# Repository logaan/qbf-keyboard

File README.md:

# QBF — compact chorded keyboard

QBF uses two identical ten-key wireless boards that can be used separately, joined flat or used one at a time. Eight portrait 1.5U keys form a close 4 × 2 grid; two 1U keys sit above and below a recessed Seeed XIAO nRF52840 Plus in column five. Key geometry is symmetric about the horizontal midpoint so the second half can rotate 180°. There is no display or external reset button.

Each main PCB and circuit-free baseplate measures **97.7 × 58.5 mm**. The accepted key layout is wider than the original 80 mm target. Four M2 mounts and a 2.25 mm border support the printed case. A protected 301055 battery sits between the main switch rows on the intact baseplate, with a side-entry JST-SH connector and a left-facing power switch tucked inside the PCB edge.

The new case has two independent trays and rims, individual snap-on covers, and one removable underside bridge. It joins the halves with controllers facing inward. Joining, separating and uncovering require no tools; initial board installation uses screws. There is no hinge. Each covered half measures **100.9 × 63.3 × 21.2 mm**. Separate the halves for ordinary straight USB cable access.

## Build files

- [Electronics guide](ergogen-kikad/README.md), [assembly requirements](ergogen-kikad/design/ASSEMBLY.md), [Ergogen source](ergogen-kikad/design/config.yaml).
- KiCad: [main PCB](ergogen-kikad/generated/pcbs/macropad.kicad_pcb), [baseplate](ergogen-kikad/generated/pcbs/baseplate.kicad_pcb), [routing preview](ergogen-kikad/generated/routing.png).
- Case: [print bundle](modular-case/generated/qbf-print-files.zip), [assembly and printing guide](modular-case/README.md), [FreeCAD](modular-case/generated/qbf_modular_case.FCStd), [dimensioned drawing](modular-case/generated/dimensions.png).
- Firmware: [standalone XIAO UF2](ergogen-kikad/generated/firmware/qbf_macropad.uf2), [shield and keymap](ergogen-kikad/config/boards/shields/qbf_macropad/), [build validation](ergogen-kikad/generated/firmware/validation.json).

Each key is wired directly to GPIO and GND, with no diode matrix. The supplied firmware makes each half an independent USB/Bluetooth keyboard and preserves the numerical test map `1 2 3 4 9 / 5 6 7 8 0`. Configure the desired chord behaviour before treating it as a Braille input device; the test map is not a completed Braille translator.

The work was completed sequentially: Ergogen layout, routed KiCad boards and assembly clearances, firmware, then case. Both boards report zero DRC violations and zero unconnected items. The electronics and case have nominal geometric checks; native KiCad renders retain all components in cap-free inspection except the ten caps. The recessed XIAO soldering process, purchased hardware, clip durability and cover strength still require a physical prototype.

## Regeneration

Follow the electronics guide to regenerate and verify the boards, then build firmware with `./scripts/build-firmware.sh /path/to/zmk-repository`. After those stages are reviewed, run `./scripts/generate-mechanical.sh`, `./modular-case/render.sh` and `./modular-case/present.sh` sequentially. Read the [case guide](modular-case/README.md) for dependencies and print orientations.

The earlier `bumper-case/` and `mechanical/` files, and AI concept images in `assets/renders/`, are historical. They do not describe or fit the current board.

## Mikoto controller diagnostics

The separate [automated test fixture](diagnostics/mikoto/README.md) uses a SuperMini nRF52840 to reset a Mikoto, enter UF2 mode and simulate four direct keyboard inputs. It includes a wiring guide, fixture code, test firmware and a macOS USB checker. Its physical fixture remains to be assembled and tested.

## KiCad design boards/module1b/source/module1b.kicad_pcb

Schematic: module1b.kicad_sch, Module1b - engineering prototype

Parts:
AE1: Antenna; AE1
C1: 4.7uF; C1; Manufacturer Part CL05A475MP5NRNC; LCSC Part C23733
C2: 100nF; C2; Manufacturer Part CL05B104KA5NNNC; LCSC Part C1525
C3: 100nF; C3; Manufacturer Part CL05B104KA5NNNC; LCSC Part C1525
C4: 100nF; C4; Manufacturer Part CL05B104KA5NNNC; LCSC Part C1525
C5: 1pF; C5; Manufacturer Part 0402CG1R0C500NT; LCSC Part C1550
C6: 15pF; C6; Manufacturer Part 0402CG150J500NT; LCSC Part C1548
C7: 15pF; C7; Manufacturer Part 0402CG150J500NT; LCSC Part C1548
C8: 1uF; C8; Manufacturer Part CL05A105KO5NNNC; LCSC Part C52923
C9: 1pF; C9; Manufacturer Part 0402CG1R0C500NT; LCSC Part C1550
C10: 100nF; C10; Manufacturer Part CL05B104KA5NNNC; LCSC Part C1525
C11: 100pF; C11; Manufacturer Part 0402CG101J500NT; LCSC Part C1546
C12: 1nF; C12; Manufacturer Part 0402B102K500NT; LCSC Part C1523
C13: 4.7uF; C13; Manufacturer Part CL05A475MP5NRNC; LCSC Part C23733
C14: 4.7uF; C14; Manufacturer Part CL05A475MP5NRNC; LCSC Part C23733
C15: 1uF; C15; Manufacturer Part CL05A105KO5NNNC; LCSC Part C52923
C16: 47nF; C16; Manufacturer Part CL05B473KO5NNNC; LCSC Part C307434
C17: 15pF; C17; Manufacturer Part 0402CG150J500NT; LCSC Part C1548
C18: 15pF; C18; Manufacturer Part 0402CG150J500NT; LCSC Part C1548
C19: 10nF; C19; Manufacturer Part CL05B103KB5NNNC; LCSC Part C15195
C20: 4.7uF; C20; Manufacturer Part CL05A475MP5NRNC; LCSC Part C23733
C21: 10uF; C21; Manufacturer Part CL10A106KP8NNNC; LCSC Part C19702
C22: 1.5pF; C22; Manufacturer Part CL05C1R5CB5NNNC; LCSC Part C170150
C23: 1uF; C23; Manufacturer Part CL05A105KO5NNNC; LCSC Part C52923
C24: 4.7uF; C24; Manufacturer Part CL05A475MP5NRNC; LCSC Part C23733
C25: 4.7uF; C25; Manufacturer Part CL05A475MP5NRNC; LCSC Part C23733
C26: 4.7uF; C26; Manufacturer Part CL05A475MP5NRNC; LCSC Part C23733
D1: BLUE; D1; Manufacturer Part 19-217/BHC-ZL1M2RY/3T; LCSC Part C72041
D3: ORANGE; D3; Manufacturer Part E6C0603SEAC1UDA; LCSC Part C375450
D5: PMEG4010CEJ; D5; Manufacturer Part PMEG4010CEJ; LCSC Part C50704
DISP1: nice!view with 5-pin 2.54mm connector; DISP1; Manufacturer Part nice!view with 5-pin 2.54mm connector
F1: 500mA hold; F1; Manufacturer Part 0402L050SLKR; LCSC Part C206938
H1: 9774020243; H1; Manufacturer Part 9774020243R
H2: 9774020243; H2; Manufacturer Part 9774020243R
H3: 9774020243; H3; Manufacturer Part 9774020243R
H4: 9774020243; H4; Manufacturer Part 9774020243R
J1: USB_C_Receptacle_USB2.0; J1; Manufacturer Part 918-418K2024S40000; LCSC Part C168688
J2: S2B-PH-SM4-TB(LF)(SN); J2; Manufacturer Part S2B-PH-SM4-TB(LF)(SN); LCSC Part C295747
L1: 3.9nH; L1; Manufacturer Part SDCL1005C3N9STDF; LCSC Part C14033
L2: 15nH; L2; Manufacturer Part SDCL1005C15NJTDF; LCSC Part C27143
L3: 10uH; L3; Manufacturer Part LBMF1608T100K; LCSC Part C87216
L4: 10uH; L4; Manufacturer Part LBMF1608T100K; LCSC Part C87216
NT1: NetTie_2; NT1
R2: 2M; R2; Manufacturer Part RC0402FR-072ML; LCSC Part C138014
R3: 2M; R3; Manufacturer Part RC0402FR-072ML; LCSC Part C138014
R4: 10M; R4; Manufacturer Part 0402WGF1005TCE; LCSC Part C26082
R5: 1.5k; R5; Manufacturer Part 0402WGF1501TCE; LCSC Part C25867
R6: 10k; R6; Manufacturer Part 0402WGF1002TCE; LCSC Part C25744
R7: 8.66k; R7; Manufacturer Part RC0402FR-078K66L; LCSC Part C185387
R8: 10k; R8; Manufacturer Part 0402WGF1002TCE; LCSC Part C25744
R9: 5.1k; R9; Manufacturer Part 0402WGF5101TCE; LCSC Part C25905
R10: 5.1k; R10; Manufacturer Part 0402WGF5101TCE; LCSC Part C25905
R11: 0R; R11; Manufacturer Part 0402WGF0000TCE; LCSC Part C17168
R12: 2M; R12; Manufacturer Part RC0402FR-072ML; LCSC Part C138014
S1: CPG135001S30; S1; Manufacturer Part CPG135001S30; LCSC Part C5333465
S2: CPG135001S30; S2; Manufacturer Part CPG135001S30; LCSC Part C5333465
S3: CPG135001S30; S3; Manufacturer Part CPG135001S30; LCSC Part C5333465
S4: CPG135001S30; S4; Manufacturer Part CPG135001S30; LCSC Part C5333465
S5: CPG135001S30; S5; Manufacturer Part CPG135001S30; LCSC Part C5333465
S6: CPG135001S30; S6; Manufacturer Part CPG135001S30; LCSC Part C5333465
S7: CPG135001S30; S7; Manufacturer Part CPG135001S30; LCSC Part C5333465
S8: CPG135001S30; S8; Manufacturer Part CPG135001S30; LCSC Part C5333465
S9: CPG135001S30; S9; Manufacturer Part CPG135001S30; LCSC Part C5333465
S10: CPG135001S30; S10; Manufacturer Part CPG135001S30; LCSC Part C5333465
S11: CPG135001S30; S11; Manufacturer Part CPG135001S30; LCSC Part C5333465
S12: CPG135001S30; S12; Manufacturer Part CPG135001S30; LCSC Part C5333465
SW1: MSK12C02; SW1; Manufacturer Part MSK12C02; LCSC Part C431540
SW2: EVQPUA02K; SW2; Manufacturer Part EVQPUA02K; LCSC Part C128539
TP1: PAD; TP1
TP2: PAD; TP2
TP3: PAD; TP3
TP4: PAD; TP4
TP5: PAD; TP5
TP6: PAD; TP6
TP7: PAD; TP7
TP8: PAD; TP8
TP9: PAD; TP9
U1: nRF52840; U1; Manufacturer Part NRF52840-QIAA-R7; LCSC Part C1851953
U2: BQ24075RGTR; U2; Manufacturer Part BQ24075RGTR; LCSC Part C15464
U3: XC6220B331MR; U3; Manufacturer Part XC6220B331MR-G; Digikey 893-1133-1-ND
U5: ESDR0502NMUTBG; U5; Manufacturer Part ESDR0502NMUTBG; LCSC Part C327480
Y1: 32MHz; Y1; Manufacturer Part Q22FA1280001800; LCSC Part C255896
Y2: 32.768 kHz; Y2; Manufacturer Part SC-20S,32.768kHz,20PPM,12.5pF; LCSC Part C97607

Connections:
ANT: AE1.1 (A), C22.2, R11.2
BAT_VOLT: C19.2, R3.2, R4.1, U1.B13 (AIN1/P0.03)
BLUE_LED: D1.2 (A), U1.AD10 (P0.15)
CC1: J1.A5 (CC1), R9.1
CC2: J1.B5 (CC2), R10.1
EXT_5V: D5.1 (K), F1.2
GND: C1.1, C2.1, C3.1, C4.2, C5.1, C6.2, C7.2, C8.2, C10.2, C11.2, C12.2, C13.2, C14.1, C15.1, C16.1, C17.1, C18.1, C19.1, C20.1, C21.1, C22.1, C23.2, C24.1, C25.1, C26.1, DISP1.2, H1.1, H2.1, H3.1, H4.1, J1.A1 (GND), J1.S1 (SHIELD), J1.S2 (SHIELD), J1.S3 (SHIELD), J1.S4 (SHIELD), J2.2, NT1.2, R2.2, R4.2, R5.1, R7.1, R8.2, R9.2, R10.2, S1.2, S2.2, S3.2, S4.2, S5.2, S6.2, S7.2, S8.2, S9.2, S10.2, S11.2, S12.2, SW1.3 (C), SW2.1, TP5.1, U1.B7 (VSS), U1.EP (VSS), U2.4 (~CE), U2.5 (EN2), U2.8 (VSS), U2.17 (VSS), U3.2 (GND), U5.1 (GND), Y1.2, Y1.4
unnamed: C5.2, L1.1, R11.1
unnamed: C6.1, U1.B24 (XC1), Y1.1
unnamed: C7.1, U1.A23 (XC2), Y1.3
unnamed: C9.2, L1.2, U1.H23 (ANT)
unnamed: C10.1, U1.C1 (DEC1)
unnamed: C11.1, U1.D23 (DEC3)
unnamed: C12.1, U1.N24 (DEC5)
unnamed: C13.1, U1.AC5 (DECUSB)
unnamed: C15.2, C16.2, L2.1, U1.B5 (DEC4), U1.E24 (DEC6)
unnamed: C17.2, U1.D2 (XL1/P0.00), Y2.1
unnamed: C18.2, U1.F2 (XL2/P0.01), Y2.2
unnamed: C23.1, F1.1, U2.13 (IN)
unnamed: D1.1 (K), R5.2
unnamed: D3.1 (K), U2.9 (~CHG)
unnamed: D3.2 (A), R6.2
unnamed: L2.2, L3.1
unnamed: L3.2, U1.B3 (DCC)
unnamed: L4.2, U1.AB2 (DCCH)
unnamed: R7.2, U2.16 (ISET)
unnamed: R8.1, U2.1 (TS)
unnamed: R3.1, R12.2
P0.02: S12.1, U1.A12 (AIN0/P0.02)
P0.04: DISP1.1, U1.J1 (AIN2/P0.04)
P0.08: DISP1.5, U1.N1 (P0.08)
P0.11: DISP1.4, U1.T2 (TRACEDATA2/P0.11)
P0.17: S1.1, U1.AD12 (P0.17)
P0.20: S2.1, U1.AD16 (P0.20)
P0.22: S3.1, U1.AD18 (P0.22)
P0.24: S4.1, U1.AD20 (P0.24)
P0.29: S9.1, U1.A10 (AIN5/P0.29)
P0.31: S10.1, U1.A8 (AIN7/P0.31)
P1.02: S6.1, U1.W24 (P1.02)
P1.04: S7.1, U1.U24 (P1.04)
P1.06: S8.1, U1.R24 (P1.06)
P1.08: S5.1, U1.P2 (P1.08)
P1.13: S11.1, U1.A16 (P1.13)
PPH_VCC: C20.2, DISP1.3, U3.5 (VOUT)
PPH_VCC_CTRL: R2.1, U1.AD8 (P0.13), U3.3 (CE)
RESET: SW2.2, U1.AC9 (P0.14), U1.AC11 (P0.16), U1.AC13 (P0.18/~RESET)
SWC: TP1.1, U1.AA24 (SWDCLK)
SWD: TP2.1, U1.AC24 (SWDIO)
SWO: TP9.1, U1.AD22 (TRACEDATA0/P1.00)
SYSOFF: SW1.2 (B), U2.15 (SYSOFF)
USB_D+: J1.A6 (D+), J1.B6 (D+), TP6.1, U1.AD6 (D+), U5.5 (D+)
USB_D-: J1.A7 (D-), J1.B7 (D-), TP4.1, U1.AD4 (D-), U5.4 (D-)
VBAT: C26.2, J2.1, R12.1, SW1.1 (A), U2.2 (BAT), U2.3 (BAT)
VBUS: C14.2, D5.2 (A), J1.A4 (VBUS), TP8.1, U1.AD2 (VBUS), U5.6 (VBUS)
VDDH: C21.2, C24.2, C25.2, R6.1, TP7.1, U1.Y2 (VDDH), U2.6 (EN1), U2.10 (OUT), U2.11 (OUT), U3.1 (VIN)
VDD_NRF: C1.2, C2.2, C3.2, C4.1, C8.1, L4.1, TP3.1, U1.A22 (VDD), U1.AD14 (VDD), U1.AD23 (VDD), U1.B1 (VDD), U1.W1 (VDD)
VSS_PA: C9.1, NT1.1, U1.F23 (VSS_PA)

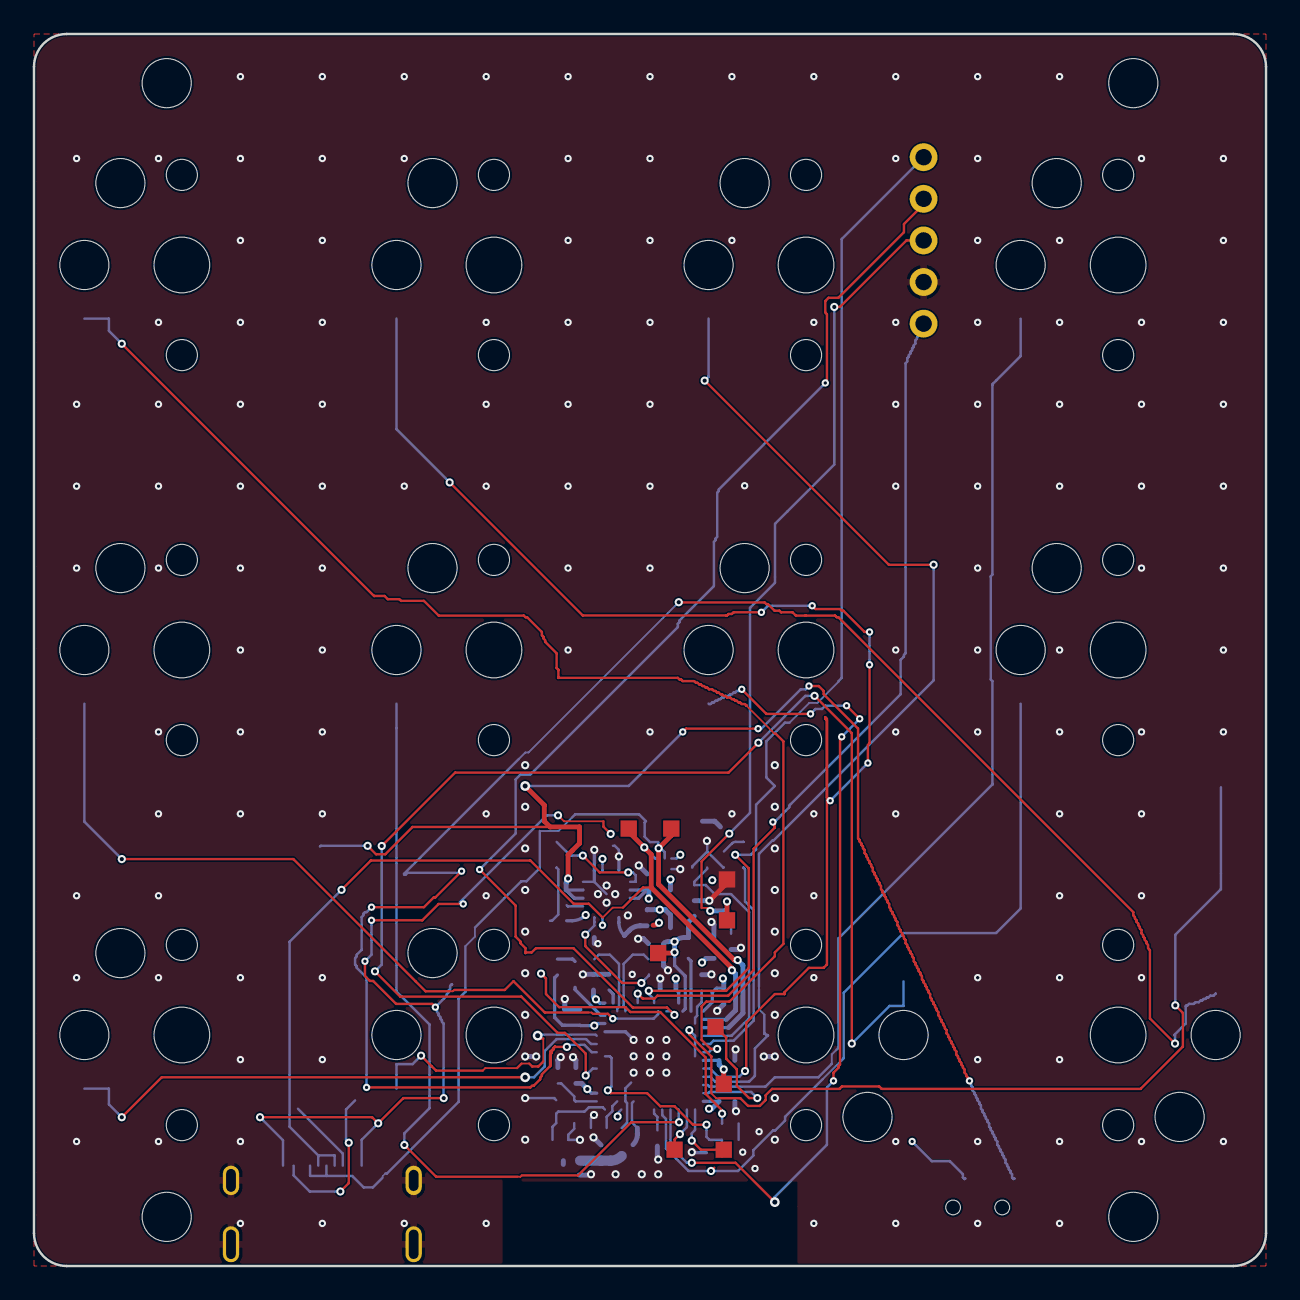
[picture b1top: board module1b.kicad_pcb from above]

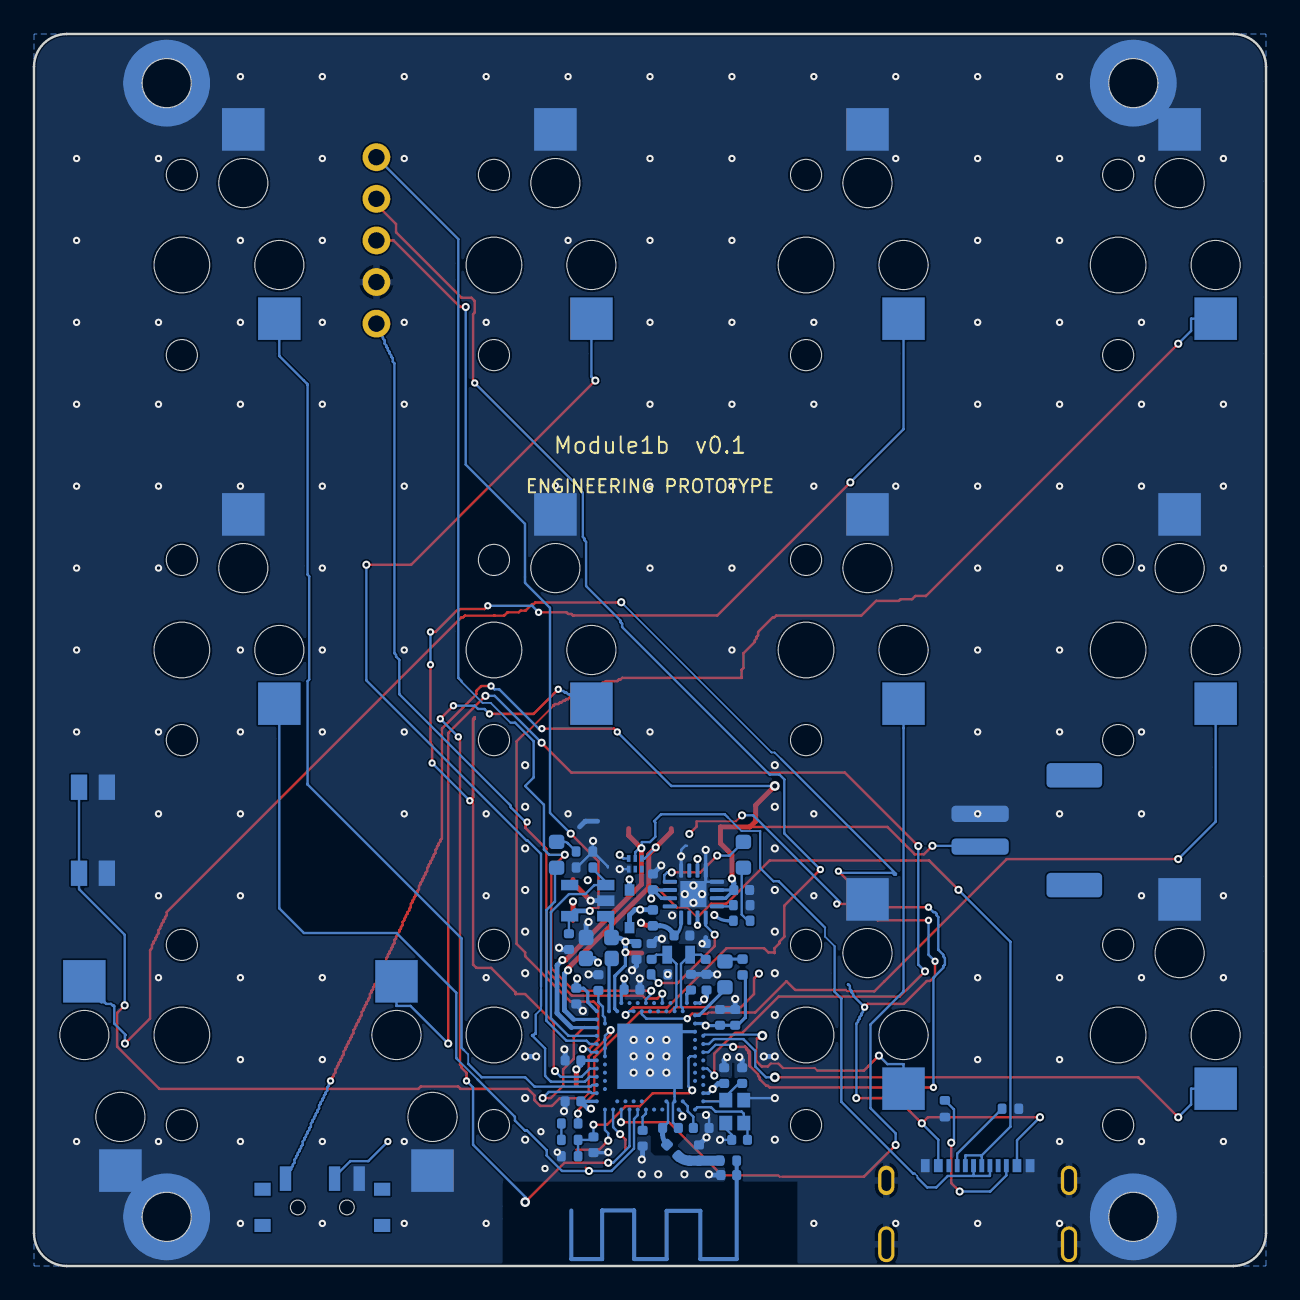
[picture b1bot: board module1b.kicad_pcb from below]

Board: 4 copper layers, 75.2 x 75.2 mm, 83 parts (74 on the bottom side), 57 nets.
